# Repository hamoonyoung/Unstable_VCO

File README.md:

# Unstable_VCO

## V1_April_2024
: This was used for the workshop at Lafayette College on April 25, 2024.

The schematic includes:

1) Voltage-Controlled Oscillator using a Schmitt Trigger
2) Uncompensated Exponential Converter
3) Mixed using Op-amp

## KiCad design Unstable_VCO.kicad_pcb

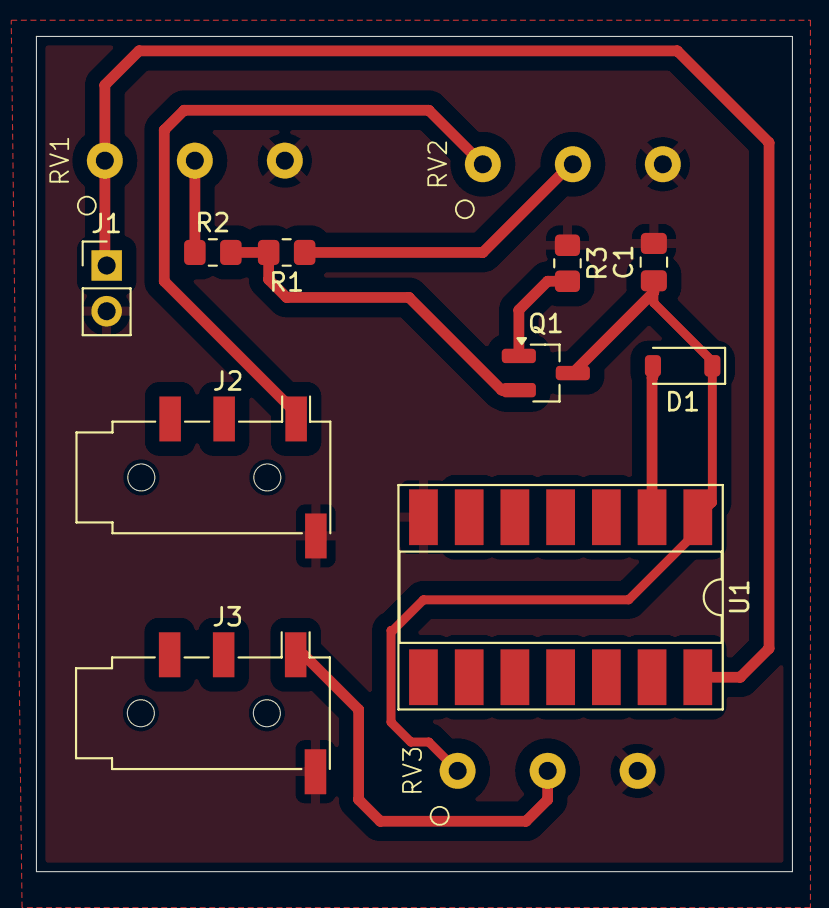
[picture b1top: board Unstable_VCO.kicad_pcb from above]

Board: 2 copper layers, 42.0 x 46.4 mm, 13 parts (0 on the bottom side), 10 nets.

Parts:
C1: 1uF; C_0805_2012Metric_Pad1.18x1.45mm_HandSolder
D1: 1N4001; D_SOD-123
J1: Conn_01x02_Pin; PinHeader_1x02_P2.54mm_Vertical
J2, J3: AudioJack4; Jack_3.5mm_PJ320D_Horizontal
Q1: 2N3904; SOT-23_Handsoldering
R1, R2: 1k; R_0805_2012Metric_Pad1.20x1.40mm_HandSolder
R3: 330; R_0805_2012Metric_Pad1.20x1.40mm_HandSolder
RV1, RV2, RV3: R_Potentiometer (100k); Potentiometer (general, 11mm, 1mm)
U1: 40106; DIP-14_W8.89mm_SMDSocket_LongPads

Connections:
+9V: J1.1, RV1.1, U1.14 (VDD)
GND: C1.2, J1.2, J2.S, J3.S, R3.1, RV1.3, RV2.3, RV3.3, U1.7 (VSS)
unnamed: D1.2 (A), U1.2
unnamed: C1.1, D1.1 (K), Q1.3 (C), RV3.1, U1.1
unnamed: J2.T, RV2.1
unnamed: J3.T, RV3.2
unnamed: Q1.2 (B), R1.2, R2.2
unnamed: Q1.1 (E), R3.2
unnamed: R1.1, RV2.2
unnamed: R2.1, RV1.2
